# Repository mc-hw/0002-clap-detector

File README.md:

# Clap detector (0002)

Clap-detecting switch

## Description

This circuit is a copy of [AVT-721/2](./AVT721_2.pdf) converted to Surface Mounted Technology.

## Assembly

The circuit should be assembled on a double-sided, SMT printed circuit board.

## Running

The device should be powered with 6-10DCV. It was intended to be powered from 6F22 9V battery connected to J1 connector.
The circuit after detecting a clap, switches D1 diode on and off. Additionally, it enables/disables K1 relay. A device
of max 230V/1000W can be enabled/disabled using J2 connector.

## Bill of materials

| Reference      | Qty | Value           | Package           |
|----------------|-----|-----------------|-------------------|
| C1,C2,C3,C4    | 4   | 100n            | 0805              |
| C5             | 1   | 100u            | 2312              |
| D1             | 1   | GREEN           | 0805              |
| D2             | 1   | RED             | 0805              |
| D3             | 1   | 1N4148          | SOD-323           |
| J1             | 1   | 9V              | JST-SH 1x2 PIN    |
| J2             | 1   | OUT             | ARK 3,5mm 1x2 PIN |
| K1             | 1   | HF49FD 012-1H11 |                   |
| MK1            | 1   | BCM-9765P       |                   |
| Q1,Q2,Q4       | 3   | BC847B          | SOT-23            |
| Q3             | 1   | BCV26           | SOT-23            |
| R1             | 1   | 10k             | 0805              |
| R2,R3,R4,R5,R8 | 5   | 100k            | 0805              |
| R6             | 1   | 47k             | 0805              |
| R7             | 1   | 10M             | 0805              |
| R9             | 1   | 1k              | 0805              |
| R10            | 1   | 4,7k            | 0805              |
| U1             | 1   | 4017            | SOP-16            |

## Implementation

# Solder mask

The amount of solder mask should not be to thin, distributing with plastic card should not be necessary,
pressure with plexi glass should be enough to distribute it.
The stencil was printed ink-down, twice. Light exposure was performed through a stencil only, no glass on top.
Each corner was exposed for 40 minutes, long edges for 20 minutes, two central points for 15 minutes each.

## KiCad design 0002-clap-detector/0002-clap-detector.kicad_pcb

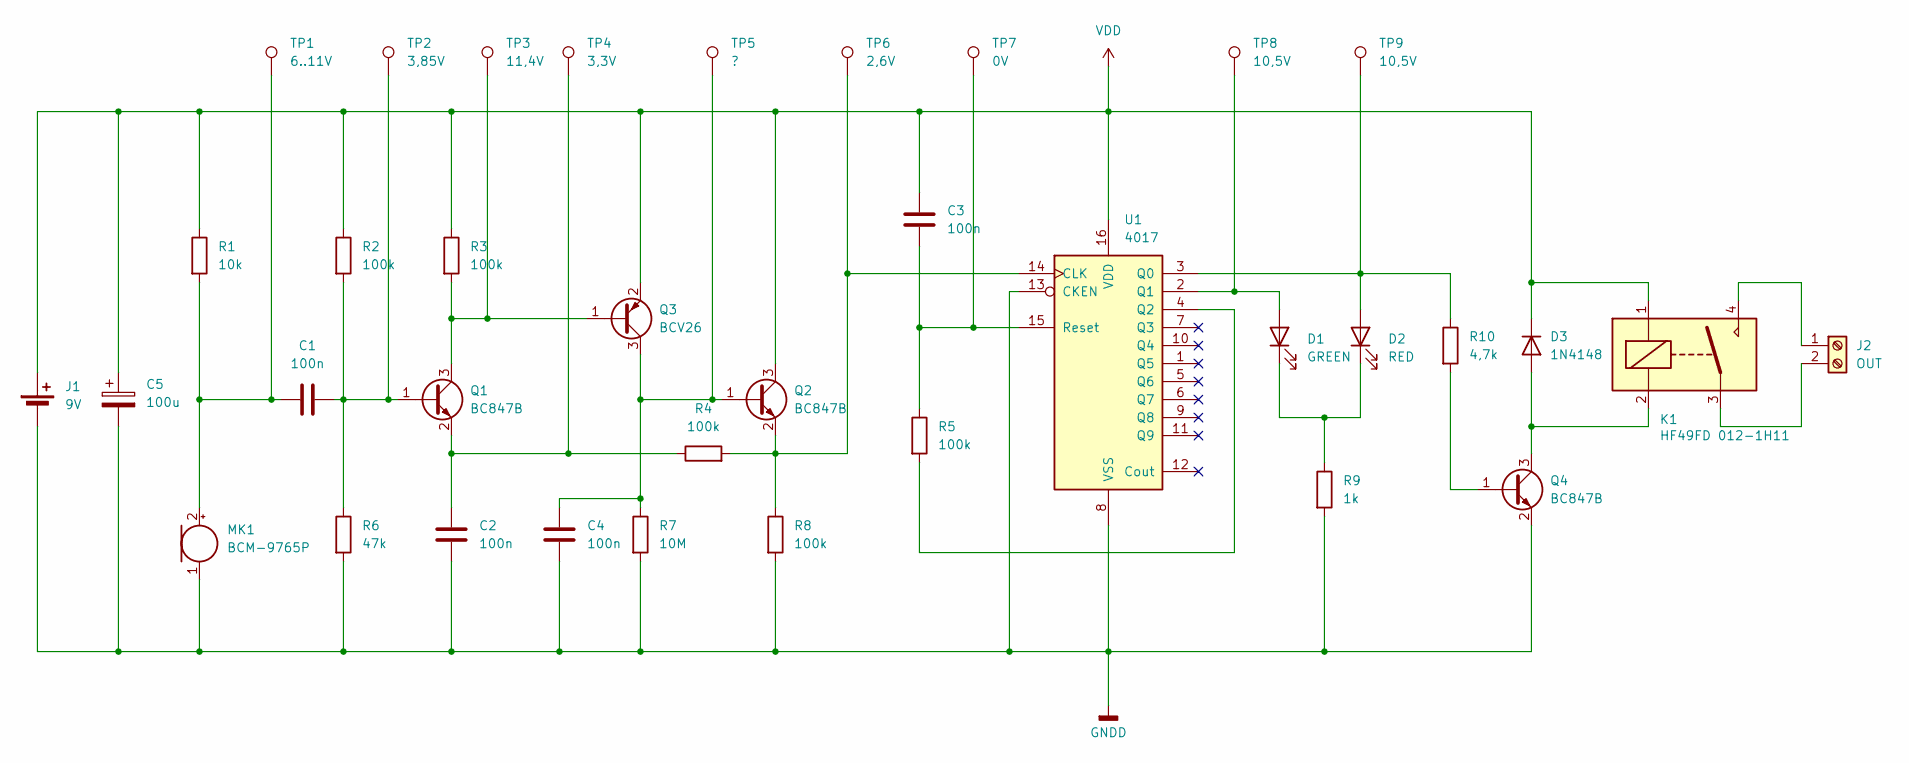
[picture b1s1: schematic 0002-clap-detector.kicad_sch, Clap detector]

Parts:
C1, C2, C3, C4: 100n; C_0805_2012Metric_Pad1.18x1.45mm_HandSolder
C5: 100u; CP_EIA-6032-28_Kemet-C_HandSolder
D1: GREEN; LED_0805_2012Metric_Pad1.15x1.40mm_HandSolder
D2: RED; LED_0805_2012Metric_Pad1.15x1.40mm_HandSolder
D3: 1N4148; D_SOD-323_HandSoldering
J1: 9V; JST_SH_BM02B-SRSS-TB_1x02-1MP_P1.00mm_Vertical
J2: OUT; TerminalBlock_MetzConnect_Type059_RT06302HBWC_1x02_P3.50mm_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
K1: HF49FD 012-1H11; Relay_SPST_TE_PCN-1xxD3MHZ
MK1: BCM-9765P; LED_D10.0mm
Q1, Q2, Q4: BC847B; SOT-23
Q3: BCV26; SOT-23
R1: 10k; R_0805_2012Metric_Pad1.20x1.40mm_HandSolder
R2, R3, R4, R5, R8: 100k; R_0805_2012Metric_Pad1.20x1.40mm_HandSolder
R6: 47k; R_0805_2012Metric_Pad1.20x1.40mm_HandSolder
R7: 10M; R_0805_2012Metric_Pad1.20x1.40mm_HandSolder
R9: 1k; R_0805_2012Metric_Pad1.20x1.40mm_HandSolder
R10: 4,7k; R_0805_2012Metric_Pad1.20x1.40mm_HandSolder
TP1: 6..11V; TestPoint_Pad_D1.5mm
TP2: 3,85V; TestPoint_Pad_D1.5mm
TP3: 11,4V; TestPoint_Pad_D1.5mm
TP4: 3,3V; TestPoint_Pad_D1.5mm
TP5: ?; TestPoint_Pad_D1.5mm
TP6: 2,6V; TestPoint_Pad_D1.5mm
TP7: 0V; TestPoint_Pad_D1.5mm
TP8, TP9: 10,5V; TestPoint_Pad_D1.5mm
U1: 4017; SOP-16_4.4x10.4mm_P1.27mm

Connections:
GNDD: C2.2, C4.2, C5.2, J1.2 (-), J1.MP, MK1.1 (-), Q4.2 (E), R6.2, R7.2, R8.2, R9.2, U1.8 (VSS), U1.13 (CKEN)
unnamed: D1.2 (A), TP8.1, U1.2 (Q1)
unnamed: D1.1 (K), D2.1 (K), R9.1
unnamed: D2.2 (A), R10.1, TP9.1, U1.3 (Q0)
unnamed: D3.2 (A), K1.2, Q4.3 (C)
unnamed: J2.1, K1.4
unnamed: J2.2, K1.3
unnamed: C1.2, MK1.2 (+), R1.2, TP1.1
unnamed: C1.1, Q1.1 (B), R2.2, R6.1, TP2.1
unnamed: Q1.3 (C), Q3.1 (B), R3.2, TP3.1
unnamed: C2.1, Q1.2 (E), R4.1, TP4.1
unnamed: C4.1, Q2.1 (B), Q3.3 (C), R7.1, TP5.1
unnamed: Q2.2 (E), R4.2, R8.1, TP6.1, U1.14 (CLK)
unnamed: Q4.1 (B), R10.2
unnamed: R5.2, U1.4 (Q2)
unnamed: C3.2, R5.1, TP7.1, U1.15 (Reset)
VDD: C3.1, C5.1, D3.1 (K), J1.1 (+), K1.1, Q2.3 (C), Q3.2 (E), R1.1, R2.1, R3.1, U1.16 (VDD)

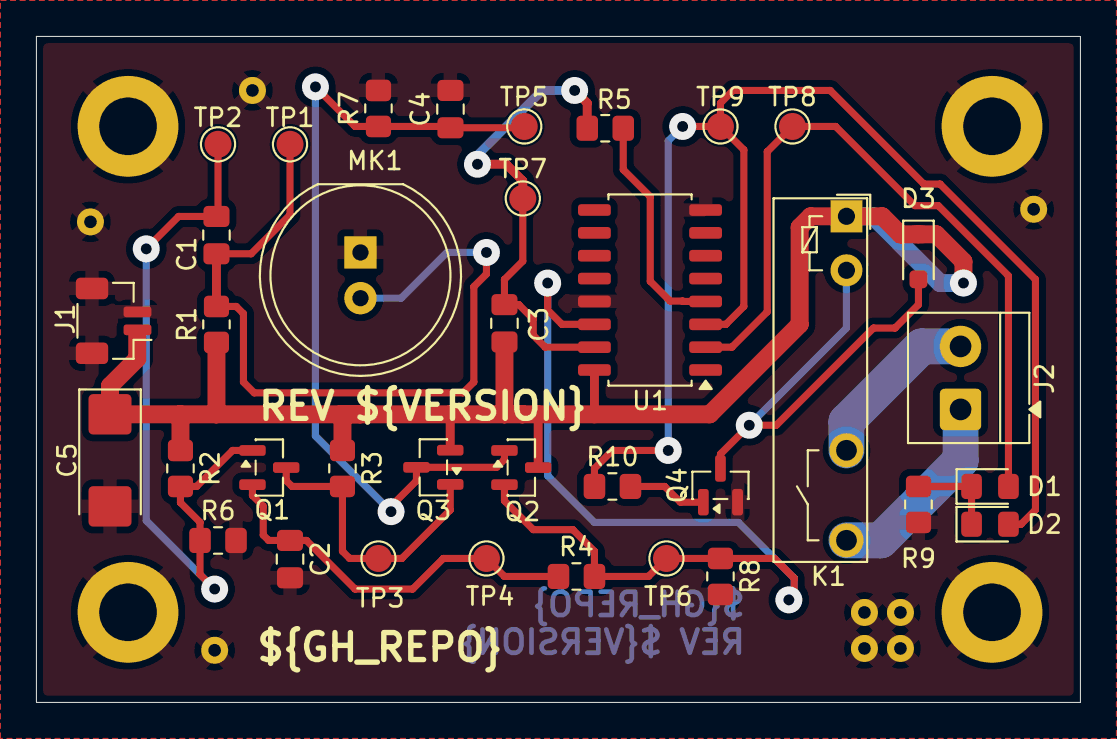
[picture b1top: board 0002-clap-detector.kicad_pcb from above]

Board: 2 copper layers, 58.0 x 37.0 mm, 36 parts (0 on the bottom side), 17 nets.

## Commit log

2025-12-10 Circuit description
2025-12-11 Circuit description (#1)
2025-12-14 KiCAD files
2025-12-14 Electric schematic
2025-12-17 Schematics
2025-12-18 Schematic (#2)
    * KiCAD files
    * Electric schematic
    * Schematics
    ---------
2025-12-19 Assign footprints to components
2025-12-20 Assign footprints to components (#3)
2025-12-21 PCB layout
2025-12-21 PCB layout refecences
2025-12-21 Small corrections
2025-12-21 PCB corrections
2025-12-21 Disable mirror
2025-12-21 Fix validation error
2025-12-23 Cleanup
2025-12-30 Pcb layout (#4)
    * PCB layout
    * PCB layout refecences
    * Small corrections
    * PCB corrections
    * Disable mirror
    * Fix validation error
2025-12-31 PCB - small correction
2026-01-01 PCB - small correction (#5)
2026-01-13 Bill of materials
2026-01-13 Bill of materials (#6)
2026-01-31 Remove solder mask documentation
2026-01-31 Solder mask hints
2026-02-04 Update schematic and pcb
2026-02-05 Small corrections (#7)
    * Remove solder mask documentation
    * Solder mask hints
    * Update schematic and pcb
    ---------
2026-03-05 Remove solder mask from fat traces
2026-03-09 Remove solder mask from fat traces (#8)
2026-03-22 Alter solder mask hints
2026-03-22 Correction
2026-03-24 Migrate to KiCAD 10
2026-03-26 Solder mask hints (#9)
    * Alter solder mask hints
    * Correction
    * Migrate to KiCAD 10
